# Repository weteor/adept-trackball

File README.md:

## xiao-mod changes:

- newly routed pcb ( [KiCAD files](hardware/electronics/adept_xiao) )
  
  - xiao rp2040 controller
  
  - two layer
  
  - components needed:
    
    - 1x seeed xiao rp2040 controller
    
    - 1x xc6206P18 LDO in SOT-23 package
    
    - 1x 100nF capacitor - 0805
    
    - 2x 1uF capacitors - 0805
    
    - 1x 10uF capacitor - 0805
    
    - 1x 39Ohm resistor - 0805
    
    - 1x 10kOhm resistor - 0805
    
    - 1x PMW3360DM-T2QU sensor (same as in orig ploopy adept)
    
    - 6x Omron D2LS-21 switches (same as in orig ploopy adept)

- modified case to support xiao dimensions ( [FreeCAD and STL files](hardware/mechanicals-xiao) )

- firmware modifications to support xiao pinout, copy [folder](firmwares/xiao_mod) to your Vial firmware folder under keyboards/ploopyco and build with: 
  `make ploopyco/adept_xiao:vial`
  or use the  `ploopyco_adept_xiao_rev1_001_vial.uf2` in the folder directly and configure the buttons in vial

---

# The Ploopy Adept Trackball

By some stroke of luck, you've made your way here. The Ploopy Adept Trackball. Your life will never be the same.

This repository contains all of the design and production files necessary to make a Ploopy Adept Trackball. We've also included some kick-ass documentation in the Wiki on how to get it made, assemble it, and program it.

What are you waiting for? Your new life awaits.

## QMK?!

Kits bought from the [Ploopy store](https://ploopy.co/product-category/trackball/adept/) come with QMK and VIA preloaded. Check out the Wiki for instructions on how to load new firmware onto your device. (It's super easy!)

The firmware hex file that ships with all Adepts is included in this repository as well, as `ploopyco_madromys_rev1_001_via.uf2`.

## Under what license is this released?

As per QMK's licensing requirements, the firmware for the Ploopy Adept Trackball is released under GPLv3. Hardware design files, including electronics and mechanical files, are released under OHL CERN v2-S. Check the respective directories for full license text.

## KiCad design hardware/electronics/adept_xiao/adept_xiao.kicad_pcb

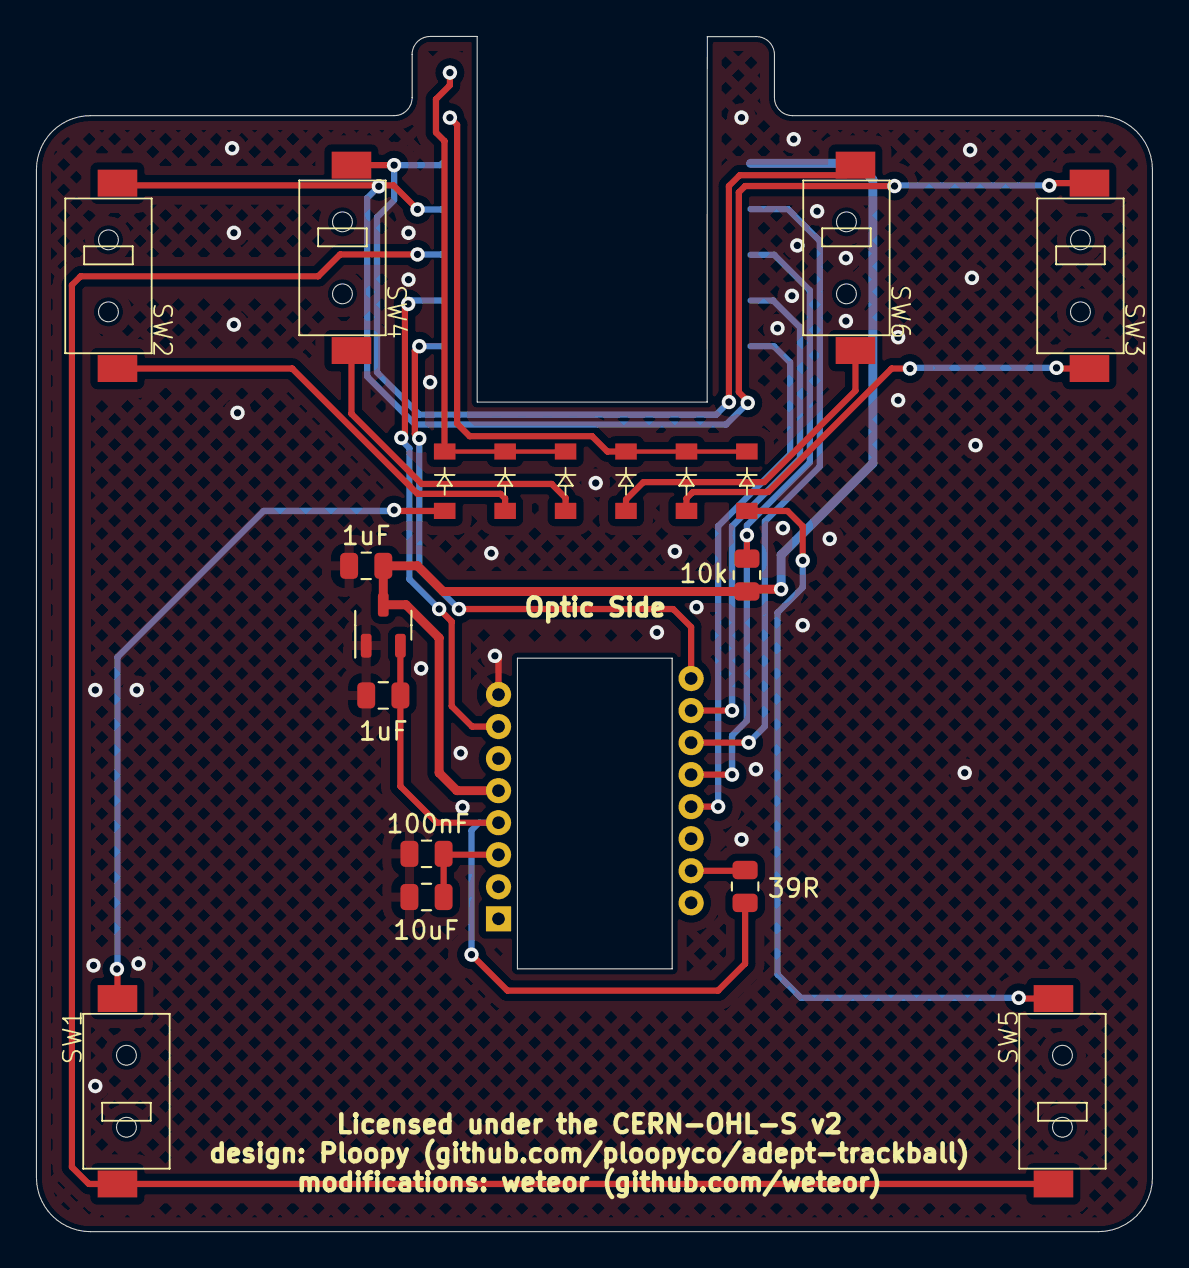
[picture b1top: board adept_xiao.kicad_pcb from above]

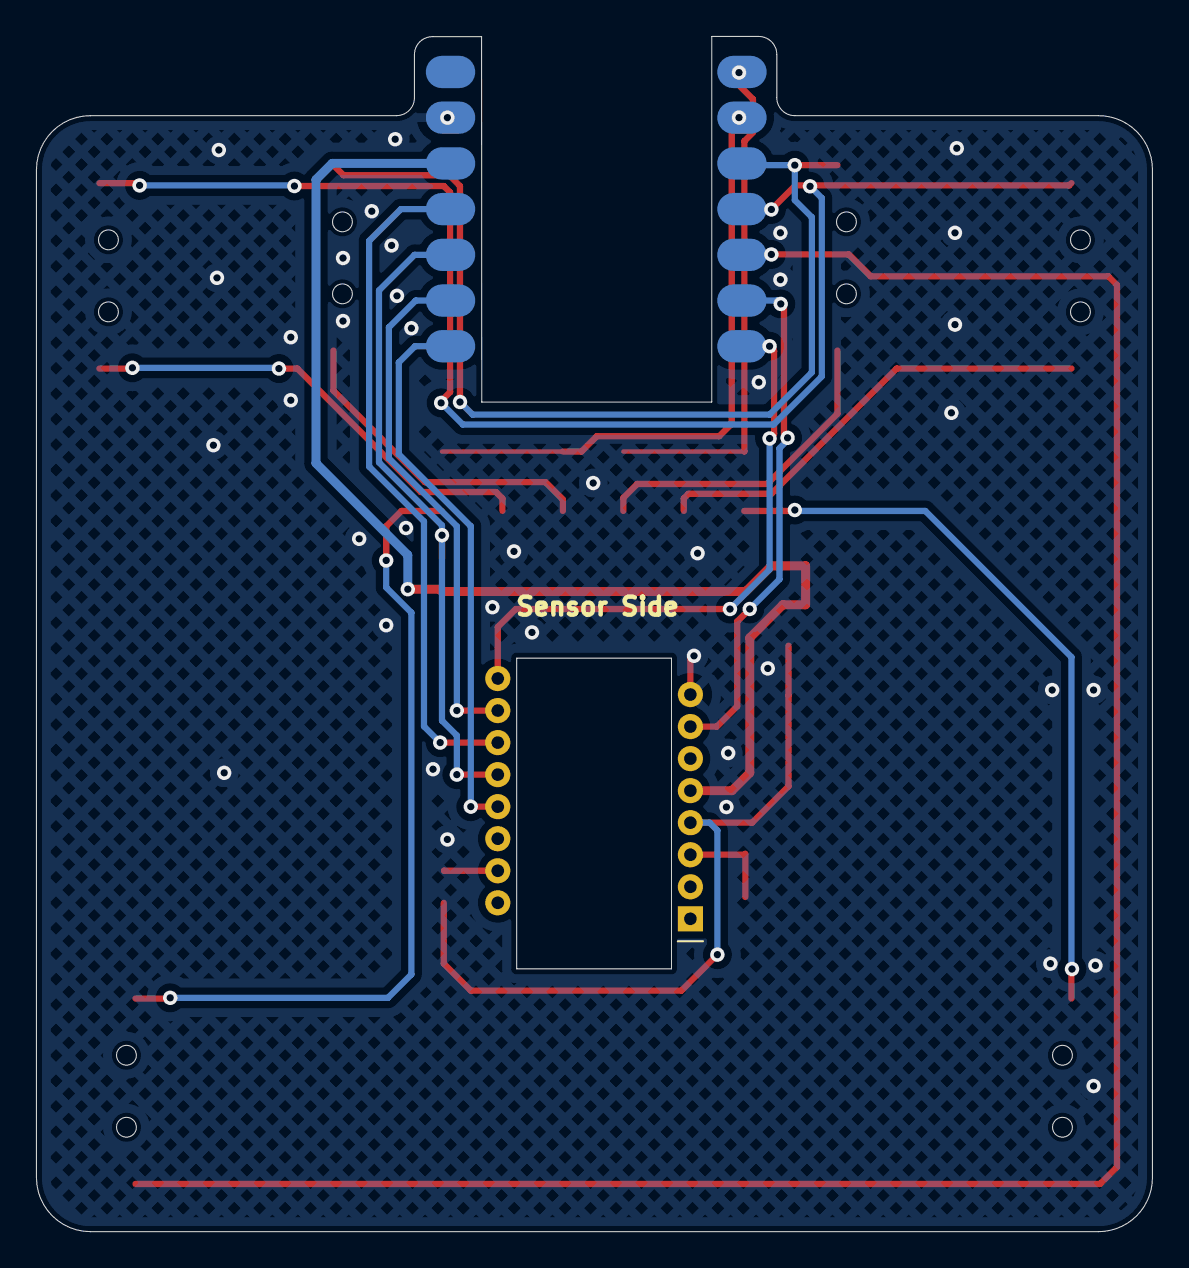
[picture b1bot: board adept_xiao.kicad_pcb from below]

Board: 2 copper layers, 62.0 x 66.4 mm, 21 parts (2 on the bottom side), 22 nets.

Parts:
C1, C2: 1uF; C_0805_2012Metric
C3: 100nF; C_0805_2012Metric
C4: 10uF; C_0805_2012Metric
D1, D2, D3, D4, D5, D6: D; D_SOD-123
R1: 39R; R_0805_2012Metric
R2: 10k; R_0805_2012Metric
SW1: Bottom_Left; Omron D2LS-21
SW2: Mid_Left; Omron D2LS-21
SW3: Mid_Right; Omron D2LS-21
SW4: Top_Left; Omron D2LS-21
SW5: Bottom_Right; Omron D2LS-21
SW6: Top_Right; Omron D2LS-21
U1: xiao-ble; xiao-ble-smd_upside_down
U2: PMW3360DM-T2QU; PXI-DIP-16
U3: XC6206PxxxMR; SOT-23-3

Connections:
+1V8: C2.1, R1.1, U2.4 (VDD), U3.2 (VO)
+3.3V: C1.1, R2.1, U1.12 (3V3), U2.5 (VDDIO), U3.3 (VI)
Button_Bottom: SW1.1 (A), SW5.1 (A), U1.5 (A8_SDA/0.04_H)
Button_Mid: SW2.1 (A), SW3.1 (A), U1.4 (A11/0.29)
Button_Top: SW4.1 (A), SW6.1 (A), U1.3 (A10/0.28)
Buttons_Left: D1.1 (K), D3.1 (K), D5.1 (K), U1.1 (A2/0.02_H)
Buttons_Right: D2.1 (K), D4.1 (K), D6.1 (K), U1.2 (A4/0.03_H)
GND: C1.2, C2.2, C3.2, C4.2, U1.13 (GND), U2.8 (GND), U3.1 (GND)
MISO: R2.2, U1.10 (A5_MISO/1.14), U2.12 (MISO)
MOSI: U1.11 (A6_MOSI/1.15), U2.11 (MOSI)
Motion: U1.7 (B8_TX/1.11), U2.9 (MOTION)
unnamed: D1.2 (A), SW1.2 (B)
unnamed: D2.2 (A), SW5.2 (B)
unnamed: D3.2 (A), SW2.2 (B)
unnamed: D4.2 (A), SW3.2 (B)
unnamed: D5.2 (A), SW4.2 (B)
unnamed: D6.2 (A), SW6.2 (B)
unnamed: R1.2, U2.15 (LED_P)
unnamed: C3.1, C4.1, U2.3 (VDDPIX)
SCK: U1.9 (A7_SCK/1.13), U2.10 (SCLK)
~CS: U1.8 (B9_RX/1.12), U2.13 (~CS)
~Reset: U1.6 (A9_SCL/0.05_H), U2.7 (~RESET)

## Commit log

2024-12-19 add xiao mod
2024-12-19 add firmware
2024-12-19 change readme
2024-12-19 fix links
2024-12-19 fix case files

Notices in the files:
hardware/electronics/adept_xiao/adept_xiao.kicad_pcb:
Licensed under the CERN-OHL-S v2
